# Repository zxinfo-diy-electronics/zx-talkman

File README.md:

# zx-talkman
DIY Speech Interface for ZX Spectrum &amp; ZX81 published in Ny Elektronik 1984 issue 10 page 36. Recreated in KiCad as close as possible to original design.

[Short demo](https://youtube.com/shorts/n-YjUCOgAG0?si=_cMUq0j-a8fil3s6) of ZX Spectrum saying 'Hello World' using the interface.

# Original construction
This is the construction as published in the magazine in 1984.

<table>
  <tr>
    <td colspan="3" align="center"></td>
  </tr>
  <tr>
    <td align="center"></td>
    <td align="center"></td>
    <td align="center"> </td>
  </tr>
  <tr>
    <td align="center">Schema</td>
    <td align="center">PCB</td>
    <td align="center">Components layout</td>
  </tr>
</table>

# Setting up KiCad 9
For this project you also need ZXInfo symbol and footprints from [here](https://github.com/zxinfo-diy-electronics/ZXINFO_LIBRARY). Follow the intructions to add the libraries to your KiCad setup.

# Recreated construction
The main goal was to get the schema redrawn in KiCad and a first try at a PCB, in order to build a version to check if everything works.

## Programming the ZX-TALKMAN
The interface is controled by outputting to port 31 (dec). On ZX Spectrum this can be done using the BASIC command out. On ZX81 you will need to write a short M/C program to send data to the interface. (May come later).

## Hello world on ZX Spectrum
```BASIC
10 READ data
20 IF data > 63 THEN OUT 31,0: STOP
30 OUT 31, data
40 GO TO 10
1000 DATA 27,51,45,53,46,52,45,21,0, 64
```

## Compatible commercial speech interfaces
OUTPUT to any port with A4 low will activate the SP0256. This means that this interface is "compatible" with the following interfaces:
- Cheetah Sweet Talker
- Fuller Orator

Some more details below.

# Planned for v1.1
Replace the CLOCK part with a crystal as described in the SP0256-AL2 documentation.

- Disbale the amplifier when the SP0256 is inactive, to reduce output noise.
- Make output SBY & LRQ line readable from computer for better control and compability with other interfaces.
- Jumper to enable/disable control of WAIT line

# version 1.0

## KNOWN issues with v1.0
It seems like the 'reset' SP0256 does not always work as intented when the computer is powered up first time. Just turn it off and on again and it should be reset correctly.

From Magazine over KiCad to PCB.

| Schema | KiCad | PCB |
| ------ | ----- | --- |
|||

## produced version of v1.0
| Building | Final | In use |
| ------ | ----- | --- |
|||

## BOM v1.0
You will need the following components:

|    Reference     | Qty |           Value           |
|------------------|-----|---------------------------|
| C1               |   1 | 820pF, ceramic            |
| C2               |   1 | 220pF, ceramic            |
| C3,C4,C9,C10,C15 |   5 | 100nF, MKT                |
| C5,C7            |   2 | 4,7uF, tantalum           |
| C6               |   1 | 470pF, ceramic            |
| C8               |   1 | 10uF, electrolytic        |
| C11,C12          |   2 | 100uF, electrolytic       |
| C13,C14          |   2 | 100nF, ceramic            |
| HT1              |   1 | Speaker0.5W/8R            |
| IC3              |   1 | SP0256-AL2 (watch out for fakes)|
| J1               |   1 | ZX_Spectrum_Connector_48K |
| Q1               |   1 | BC548                     |
| R1               |   1 | 4.7K                      |
| R2,R10           |   2 | 100R                      |
| R3               |   1 | 330R                      |
| R4               |   1 | 100K                      |
| R5               |   1 | 33K                       |
| R6               |   1 | 1M                        |
| R7               |   1 | 4,7K                      |
| R8               |   1 | 10K, logarithmic          |
| R9               |   1 | 10R                       |
| U1               |   1 | 74LS00                    |
| U2               |   1 | 74LS32                    |
| U3               |   1 | LM386                     |

# Other interfaces using SP0256 - and what I know about them :-)

## Currah uSpeech
Probaly the most popular speech interface for ZX Spectrum is the [Currah uSpeech](https://spectrumcomputing.co.uk/entry/8067/ZX-Spectrum/Currah_MicroSpeech), wich had suport in multiple [games](https://spectrumcomputing.co.uk/entry/1000081/Hardware/Currah_MicroSpeech). It comes with it's own overlay ROM and hardware to control it - making it easy to use from BASIC. Looks like it can be controlled by your own code, but that I need to investigate.

## Cheetah Sweet Talker
The [Sweet Talker](https://spectrumcomputing.co.uk/entry/1000063/Hardware/Cheetah_Sweet_Talker) is a simple interface, almost like this DIY - in fact the demo program [Chatbox](https://spectrumcomputing.co.uk/entry/10467/ZX-Spectrum/Chatbox) - can be used with this interface right out of the box (mainly because of simple address decoding). You can see it demonstraded in this [video](https://youtube.com/shorts/8_oEiTdBw0U)
- Output data to port 7
- NEEDS SBY to WAIT connection

## dk'tronics speech synthesiser
Another speech interface is the dk'tronics [speech synthesiser](https://spectrumcomputing.co.uk/entry/1000128/Hardware/DKTronics_Speech_Synthesiser). According to the manual, it's controlled by:
- Output data to port 127
- Read status from port 127 (data = 127 = READY)
Comes with a program to make it easy to use from BASIC, need to investigate it further - to see if it will work with this interface.

## Fuller Orator
Fuller [Orator](https://spectrumcomputing.co.uk/entry/1000165/Hardware/Fuller_Orator) - yes, it runs the [demonstration](https://youtube.com/shorts/HEt_V7jbKws?si=R-SY6JT0dKBFEpfD) program as well.
- Output data to port 159
- Works best if SBY to WAIT is removed

### Games supporting Fuller Orator
- [Jungle Fever](https://spectrumcomputing.co.uk/entry/2660/ZX-Spectrum/Jungle_Fever)
- [Chuckie Egg](https://spectrumcomputing.co.uk/entry/958/ZX-Spectrum/Chuckie_Egg)
- [Ziggurat](https://spectrumcomputing.co.uk/entry/5855/ZX-Spectrum/Ziggurat)
- [Key Speaker](https://spectrumcomputing.co.uk/entry/13384/ZX-Spectrum/Key_Speaker) (A bit like Currah Speech, talks while you type)
- [Spectrum Voice Chess](https://spectrumcomputing.co.uk/entry/5599/ZX-Spectrum/Spectrum_Voice_Chess) (Orator version, speaks to fast - needs to wait for chip ready?)
- [Dimension Destructor](https://spectrumcomputing.co.uk/entry/1394/ZX-Spectrum/Dimension_Destructors) (NOT confirmed to work)

## Datel Vox Box

## William Stuart Chatterbox I & II

# Tools and useful links
- SP0256-AL2 [Datasheet](https://www.bitsavers.org/components/gi/speech/General_Instrument_-_SP0256A-AL2_datasheet_(Radio_Shack_276-1784)_-_Apr1984.pdf)
- Be aware [Genuine vs Counterfeit.](https://www.smbaker.com/counterfeitfakejustplainbad-sp0256a-al2-chips)
- Online [text to speech](https://greg-kennedy.com/sp0256-tts/)

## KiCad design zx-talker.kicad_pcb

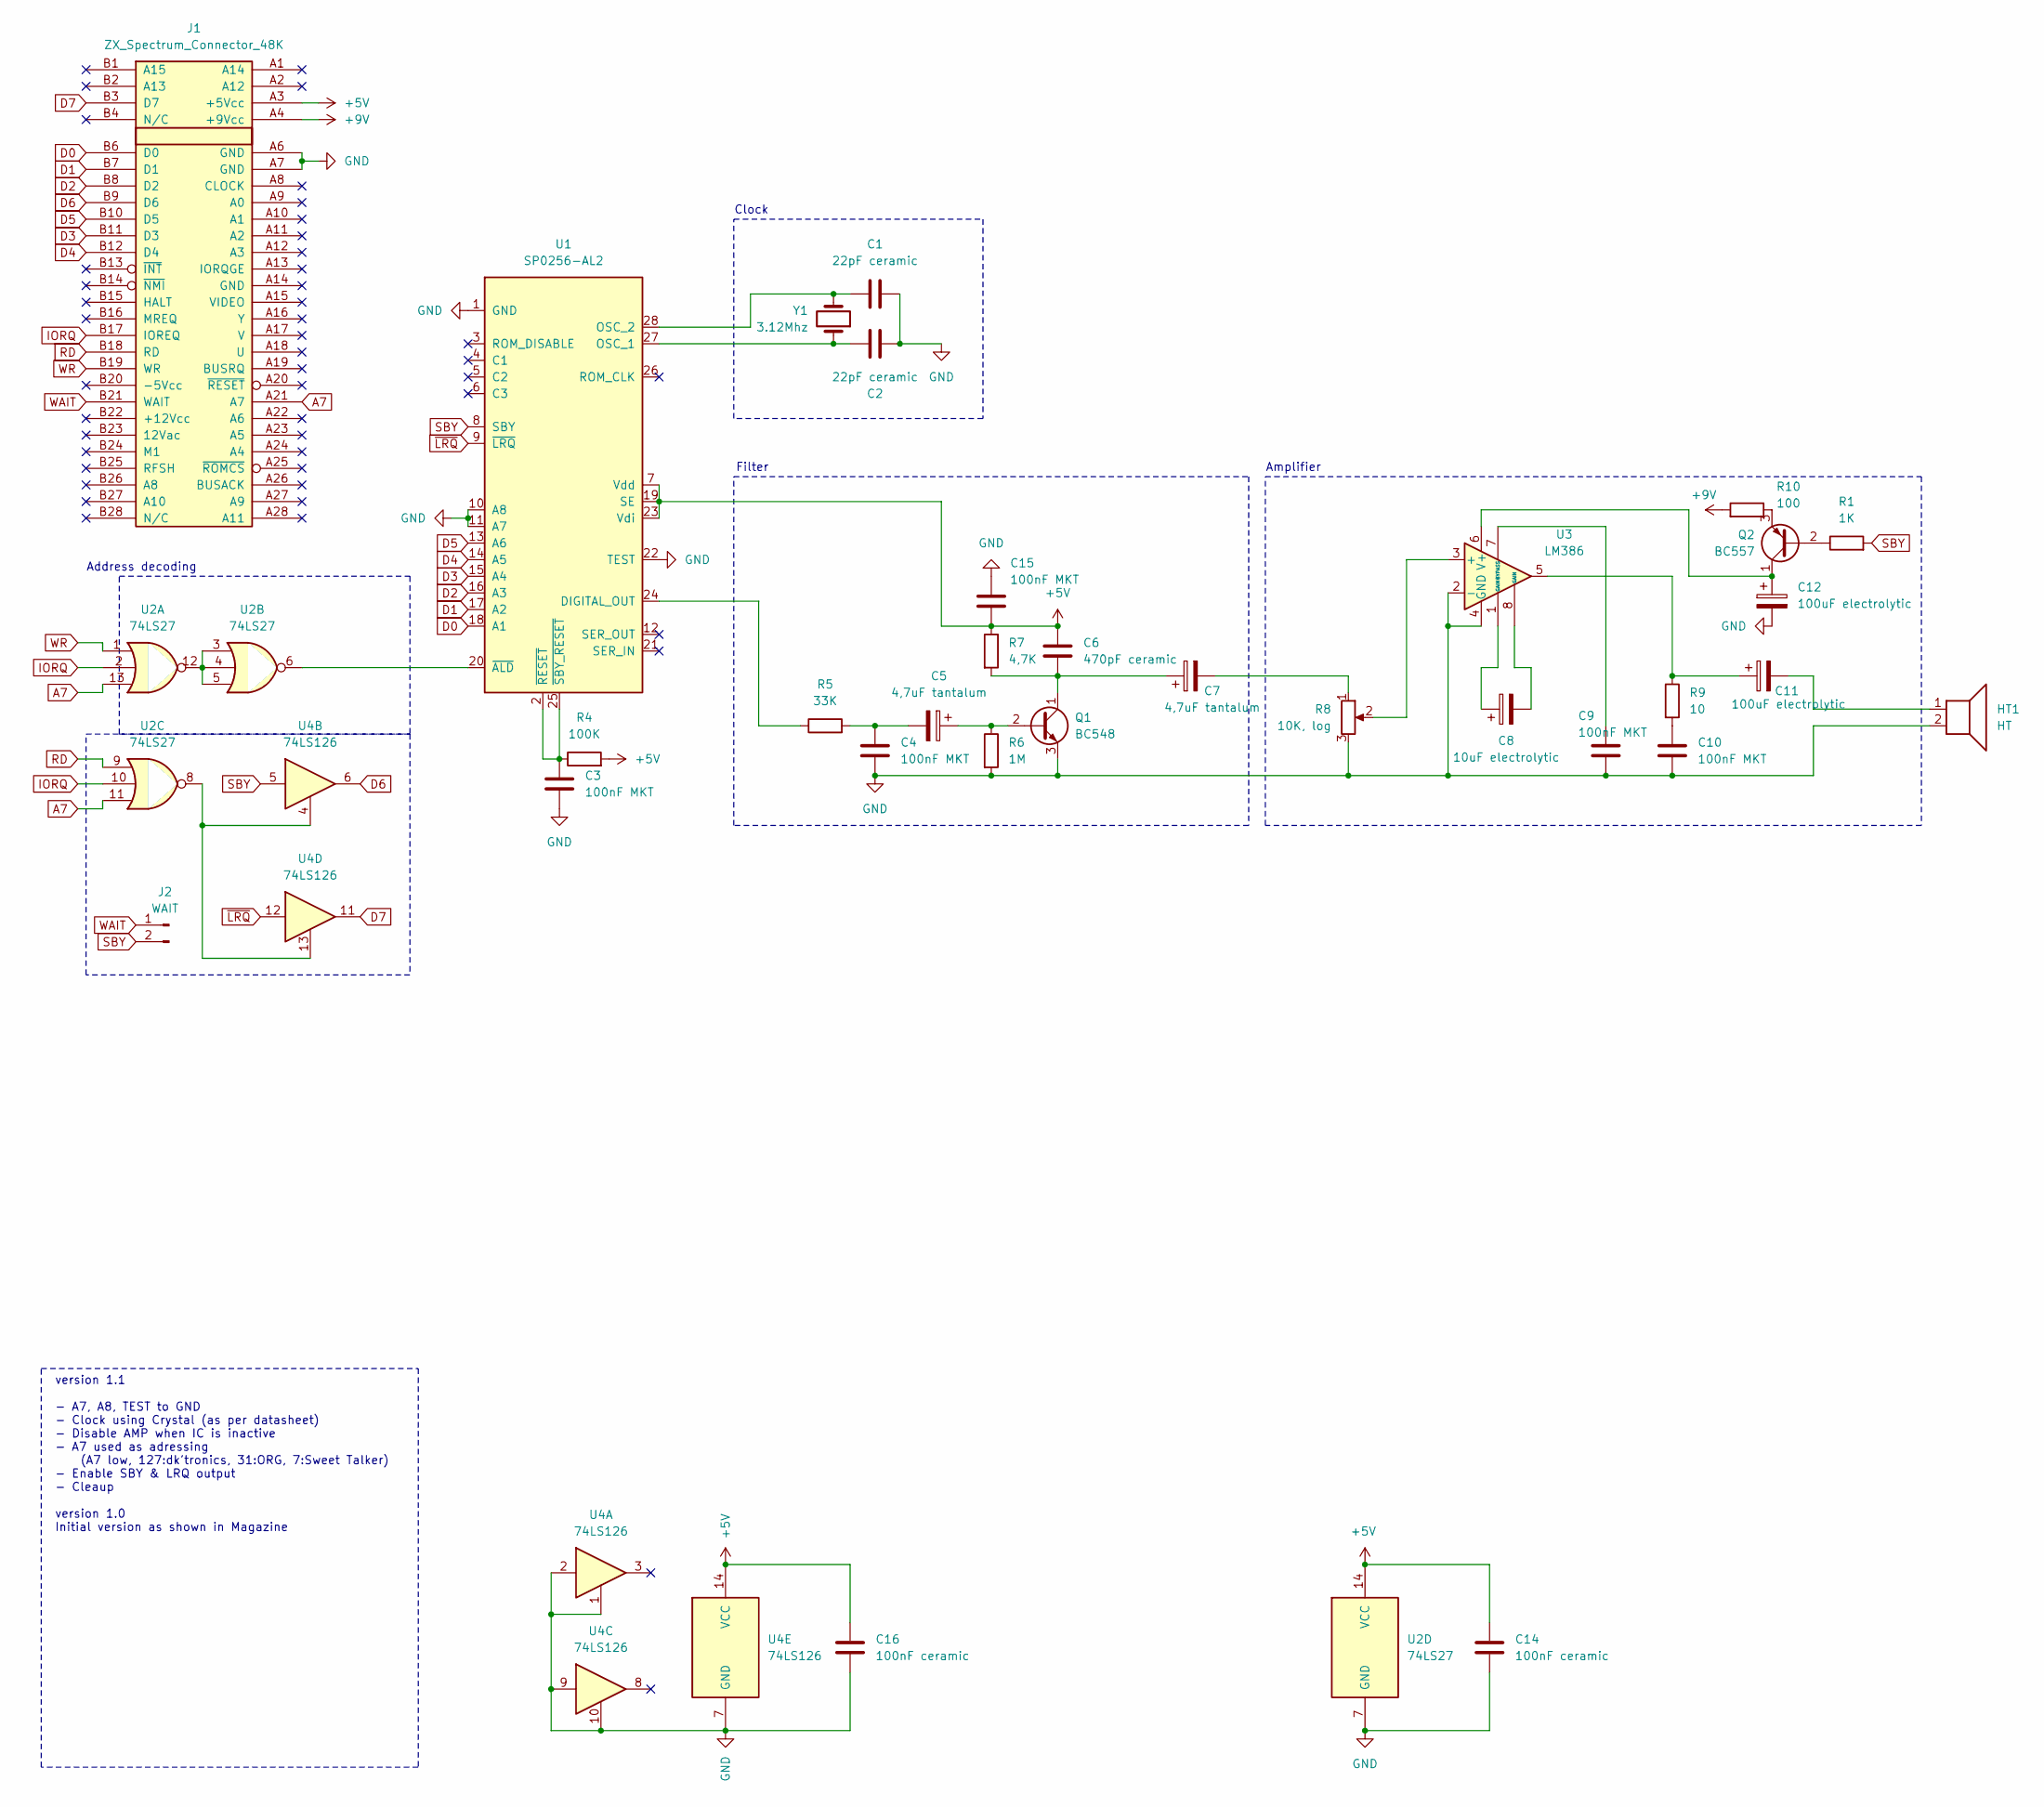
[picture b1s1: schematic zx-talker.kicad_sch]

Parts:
C1, C2: 22pF ceramic; C_Rect_L7.0mm_W2.5mm_P5.00mm
C3, C4, C9, C10, C15: 100nF MKT; C_Rect_L7.0mm_W2.5mm_P5.00mm
C5, C7: 4,7uF tantalum; CP_Radial_Tantal_D4.5mm_P5.00mm
C6: 470pF ceramic; C_Disc_D4.3mm_W1.9mm_P5.00mm
C8: 10uF electrolytic; CP_Radial_D5.0mm_P2.50mm
C11, C12: 100uF electrolytic; CP_Radial_D5.0mm_P2.50mm
C14, C16: 100nF ceramic; C_Disc_D3.0mm_W1.6mm_P2.50mm
HT1: HT; PinHeader_1x02_P2.54mm_Horizontal
J1: ZX_Spectrum_Connector_48K; EDGE_ZX_SPECTRUM
J2: WAIT; PinHeader_1x02_P2.54mm_Horizontal
Q1: BC548; TO-92_Inline
Q2: BC557; TO-92_Inline
R1: 1K; R_Axial_DIN0207_L6.3mm_D2.5mm_P10.16mm_Horizontal
R4: 100K; R_Axial_DIN0207_L6.3mm_D2.5mm_P10.16mm_Horizontal
R5: 33K; R_Axial_DIN0207_L6.3mm_D2.5mm_P10.16mm_Horizontal
R6: 1M; R_Axial_DIN0207_L6.3mm_D2.5mm_P10.16mm_Horizontal
R7: 4,7K; R_Axial_DIN0207_L6.3mm_D2.5mm_P10.16mm_Horizontal
R8: 10K, log; PinHeader_1x03_P2.54mm_Horizontal
R9: 10; R_Axial_DIN0207_L6.3mm_D2.5mm_P10.16mm_Horizontal
R10: 100; R_Axial_DIN0207_L6.3mm_D2.5mm_P10.16mm_Horizontal
U1: SP0256-AL2; DIP-28_W15.24mm_Socket
U2: 74LS27; DIP-14_W7.62mm
U3: LM386; DIP-8_W7.62mm
U4: 74LS126; DIP-14_W7.62mm
Y1: 3.12Mhz; Crystal_HC49-U_Vertical

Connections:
+5V: C6.1, C14.1, C15.2, C16.1, J1.A3 (+5Vcc), R4.2, R7.1, U1.7 (Vdd), U1.19 (SE), U1.23 (Vdi), U2.14 (VCC), U4.14 (VCC)
+9V: J1.A4 (+9Vcc), R10.2
A7: J1.A21 (A7), U2.11, U2.13
D0: J1.B6 (D0), U1.18 (A1)
D1: J1.B7 (D1), U1.17 (A2)
D2: J1.B8 (D2), U1.16 (A3)
D3: J1.B11 (D3), U1.15 (A4)
D4: J1.B12 (D4), U1.14 (A5)
D5: J1.B10 (D5), U1.13 (A6)
D6: J1.B9 (D6), U4.6
D7: J1.B3 (D7), U4.11
GND: C1.2, C2.1, C3.2, C4.2, C9.2, C10.2, C12.2, C14.2, C15.1, C16.2, HT1.2, J1.A6 (GND), J1.A7 (GND), Q1.3 (E), R6.2, R8.3, U1.1 (GND), U1.10 (A8), U1.11 (A7), U1.22 (TEST), U2.7 (GND), U3.2 (-), U3.4 (GND), U4.1, U4.2, U4.7 (GND), U4.9, U4.10
IORQ: J1.B17 (IOREQ), U2.2, U2.10
unnamed: C4.1, C5.2, R5.2
unnamed: C7.2, R8.1
unnamed: C8.1, U3.1 (GAIN)
unnamed: C8.2, U3.8 (GAIN)
unnamed: C10.1, R9.2
unnamed: C11.1, R9.1, U3.5
unnamed: C11.2, HT1.1
unnamed: C5.1, Q1.2 (B), R6.1
unnamed: C6.2, C7.1, Q1.1 (C), R7.2
unnamed: Q2.2 (B), R1.1
unnamed: C12.1, Q2.1 (C), U3.6 (V+)
unnamed: Q2.3 (E), R10.1
unnamed: R5.1, U1.24 (DIGITAL_OUT)
unnamed: C2.2, U1.27 (OSC_1), Y1.1
unnamed: C1.1, U1.28 (OSC_2), Y1.2
unnamed: U1.20 (~ALD), U2.6
unnamed: C3.1, R4.1, U1.2 (~RESET), U1.25 (~SBY_RESET)
unnamed: U2.8, U4.4, U4.13
unnamed: U2.3, U2.4, U2.5, U2.12
unnamed: R8.2, U3.3 (+)
unnamed: C9.1, U3.7 (BYPASS)
RD: J1.B18 (RD), U2.9
SBY: J2.2, R1.2, U1.8 (SBY), U4.5
WAIT: J1.B21 (WAIT), J2.1
WR: J1.B19 (WR), U2.1
~LRQ: U1.9 (~LRQ), U4.12

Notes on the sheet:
Amplifier
version 1.1 - A7, A8, TEST to GND - Clock using Crystal (as per datasheet) - Disable AMP when IC is inactive - A7 used as adressing (A7 low, 127:dk'tronics, 31:ORG, 7:Sweet Talker) - Enable SBY & LRQ output - Cleaup version 1.0 Initial version as shown in Magazine
Clock
Address decoding
Filter

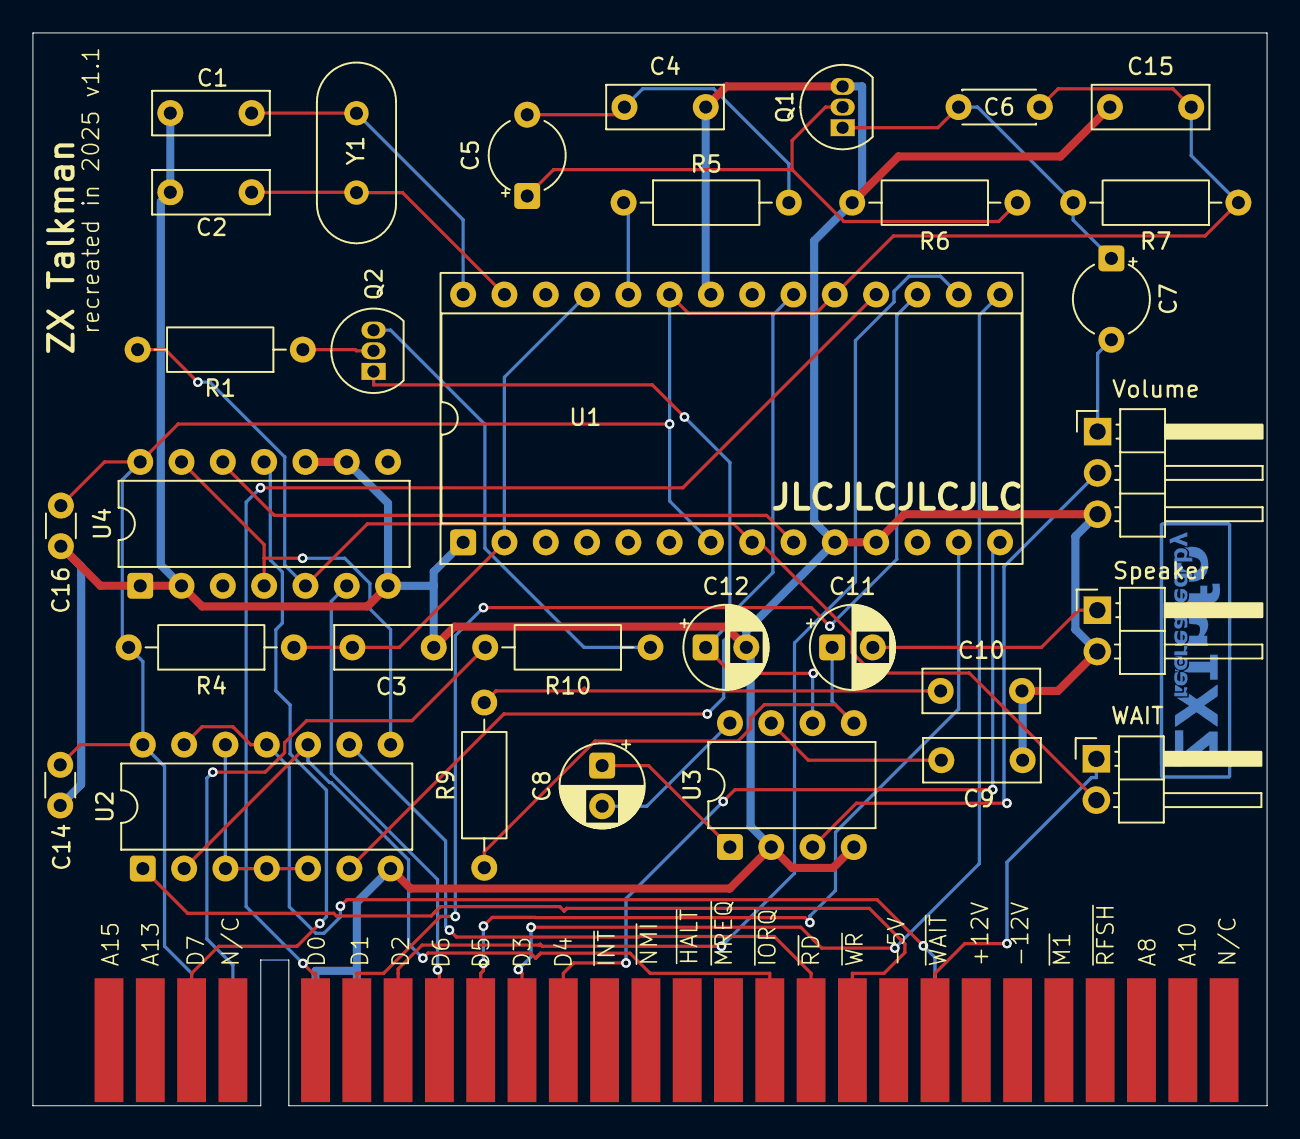
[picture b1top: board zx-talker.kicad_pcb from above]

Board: 2 copper layers, 75.9 x 66.0 mm, 34 parts (1 on the bottom side), 39 nets.

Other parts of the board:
G200: LOGO; ZXInfo_kicad_logo_copper_16.5x5

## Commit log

2026-03-22 Add BOM v1.0 section to README
    Added BOM v1.0 section with required components.
2026-03-22 Initial version
2026-03-22 Update README with KiCad setup instructions
    Added instructions for setting up KiCad 9 and required libraries.
2026-03-22 Update README with planned features for v1.1
    Added planned features for version 1.1, including replacing the CLOCK part and adding RCA for audio out.
2026-03-22 Update README with audio output details
    Disable the amplifier when the SP0256 is inactive to reduce output noise.
2026-03-22 Update README.md for KiCad setup and versioning
2026-03-22 Add demo link to README for ZX Spectrum project
    Added a link to a short demo of the ZX Spectrum using the speech interface.
2026-03-22 Fix wording in README description
2026-03-24 updated with improvements
2026-03-25 Update README with compatible speech interfaces
    Added section on compatible commercial speech interfaces and details about the Fuller Orator.
2026-04-14 Update README.md
    Updated Fuller Orator section
2026-04-14 Update description for Spectrum Voice Chess
    Clarified description of Spectrum Voice Chess regarding speech speed.
2026-04-14 Update README with SBY connection note
    Added note about SBY to WAIT connection for Cheetah Sweet Talker.
2026-04-14 Update README with planned features for v1.1
    Removed redundant notes and clarified planned features for v1.1.
